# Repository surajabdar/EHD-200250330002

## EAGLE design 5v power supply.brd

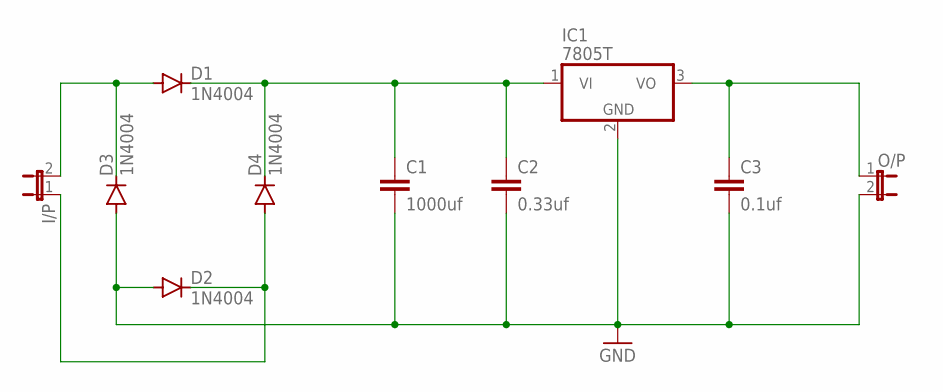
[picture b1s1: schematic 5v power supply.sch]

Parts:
C1: 1000uf; C2.5-3
C2: 0.33uf; C2.5-3
C3: 0.1uf; C2.5-3
D1, D2, D3, D4: 1N4004; DO41-10
I/P: JP1E; JP1
IC1: 7805T; TO220H
O/P: JP1E; JP1

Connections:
GND: C1.2, C2.2, C3.2, D2.A, D3.A, IC1.2 (GND), O/P.2
unnamed: D1.A, D3.C, I/P.2
unnamed: C1.1, C2.1, D1.C, D4.C, IC1.1 (VI)
unnamed: D2.C, D4.A, I/P.1
unnamed: C3.1, IC1.3 (VO), O/P.1

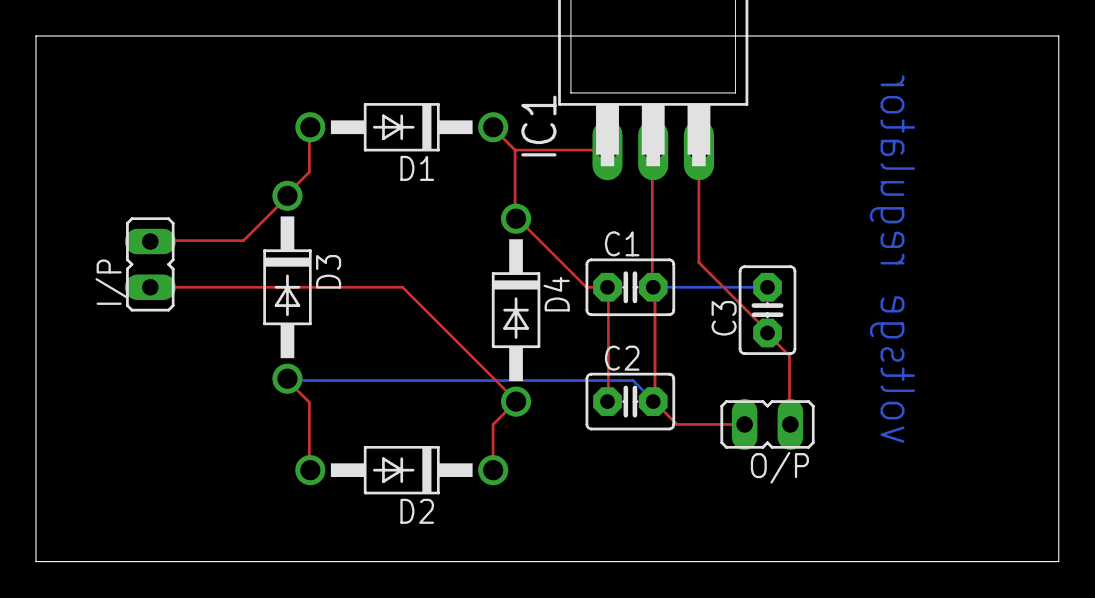
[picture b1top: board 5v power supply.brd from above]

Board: 2 copper layers, 56.8 x 29.2 mm, 10 parts (0 on the bottom side), 5 nets.

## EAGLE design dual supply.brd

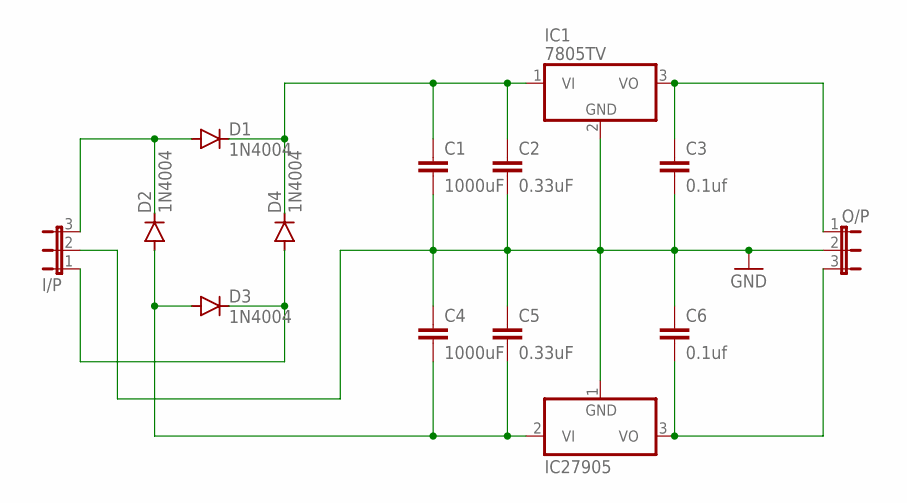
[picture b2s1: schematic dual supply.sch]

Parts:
C1, C4: 1000uF; C2.5-3
C2, C5: 0.33uF; C2.5-3
C3, C6: 0.1uf; C2.5-3
D1, D2, D3, D4: 1N4004; DO41-10
I/P: JP2E; JP2
IC1: 7805TV; TO220V
IC27905: 7905T; TO220H
O/P: JP2E; JP2

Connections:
GND: C1.2, C2.2, C3.2, C4.1, C5.1, C6.1, I/P.2, IC1.2 (GND), IC27905.1 (GND), O/P.2
unnamed: D1.A, D2.C, I/P.3
unnamed: C1.1, C2.1, D1.C, D4.C, IC1.1 (VI)
unnamed: D3.C, D4.A, I/P.1
unnamed: C4.2, C5.2, D2.A, D3.A, IC27905.2 (VI)
unnamed: C3.1, IC1.3 (VO), O/P.1
unnamed: C6.2, IC27905.3 (VO), O/P.3

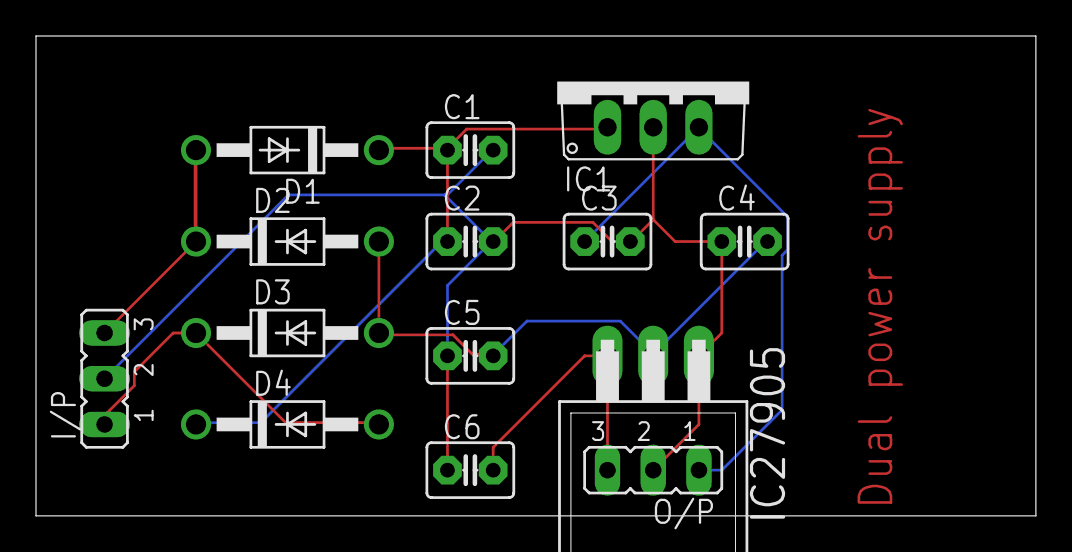
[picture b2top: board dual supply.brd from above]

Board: 2 copper layers, 55.5 x 26.7 mm, 14 parts (0 on the bottom side), 7 nets.
